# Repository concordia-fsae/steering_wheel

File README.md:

### This code now has Travis CI setup for continuous integration testing!
Current build status: 

# Setup Instructions
  1. Setup PlatformIO in IDE of choice (i.e. VSCode)
  2. Navigate to PlatformIO install directory (usually User_folder/.platformio)
  3. Enter `packages` directory and rename `framework-arduinoststm32-maple` to `framework-arduinoststm32-maple-bak`
  4. Clone [Roger Clark's repo](https://github.com/rogerclarkmelbourne/Arduino_STM32) into the packages directory (`git clone https://github.com/rogerclarkmelbourne/Arduino_STM32.git framework-arduinoststm32-maple`)
  5. Copy `platformio-build-stm32f4.py` and `platformio-build-stm32f1.py` from `framework-arduinoststm32-maple-bak/tools` to `framework-arduinoststm32-maple/tools`
  6. Compile successfully (hopefully)

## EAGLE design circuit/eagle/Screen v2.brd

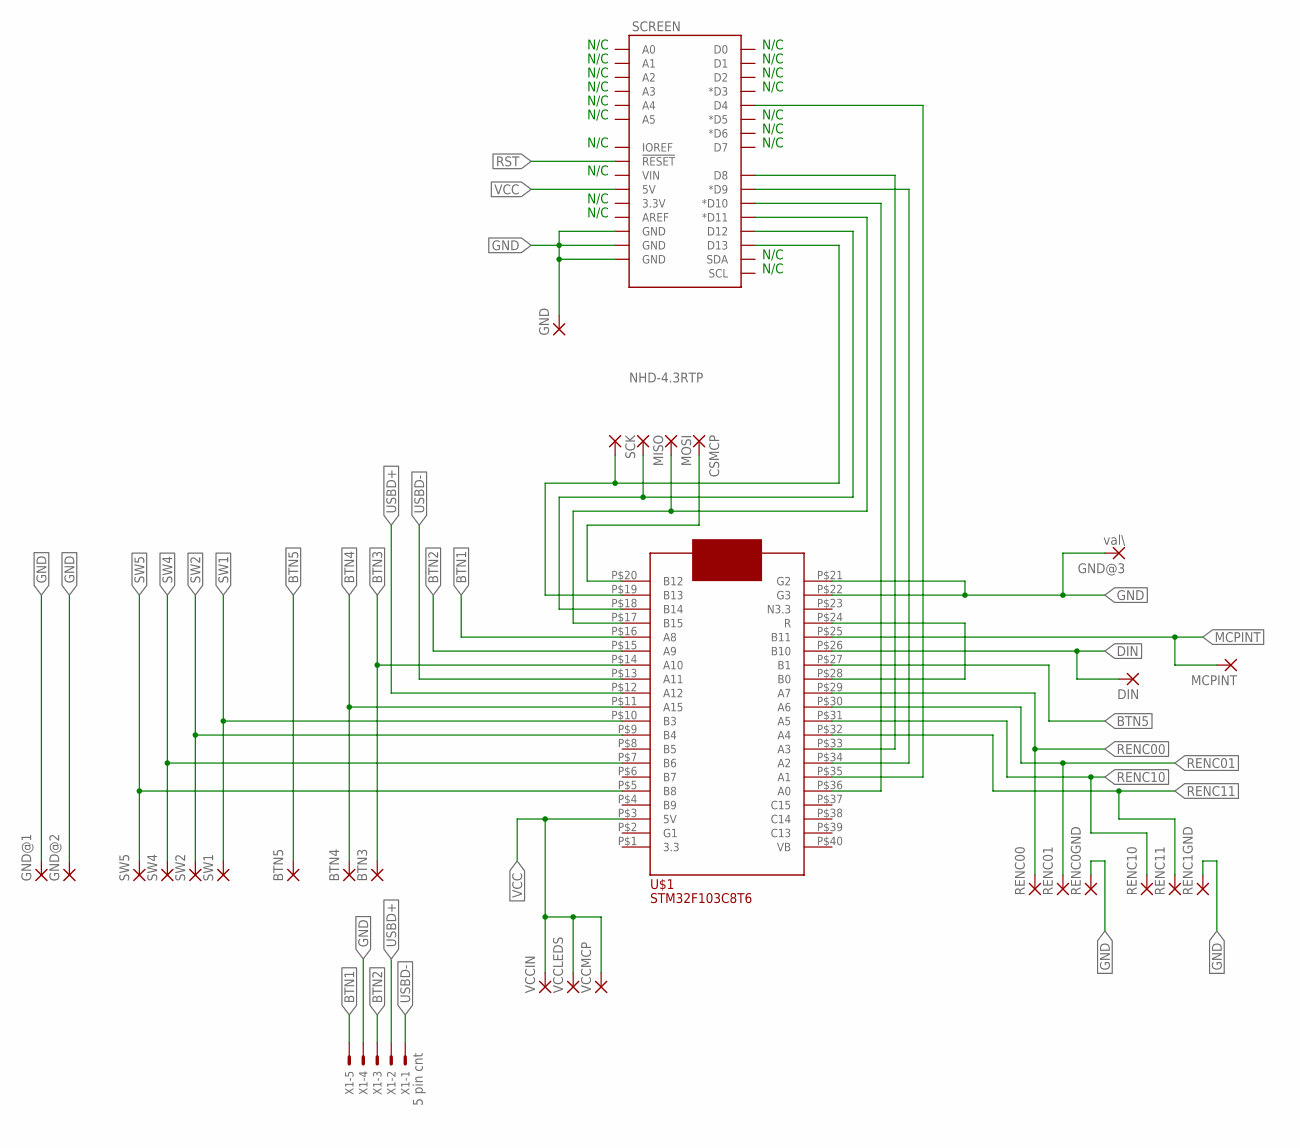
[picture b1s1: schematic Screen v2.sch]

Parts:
BTN3, BTN4, BTN5: SMD5; SMD2,54-5,08
CSMCP: SMD5; SMD2,54-5,08
DIN: SMD5; SMD2,54-5,08
GND: SMD5; SMD2,54-5,08
GND@1, GND@2: SMD5; SMD2,54-5,08
GND@3: val\; SMD2,54-5,08
MCPINT: SMD5; SMD2,54-5,08
MISO: SMD5; SMD2,54-5,08
MOSI: SMD5; SMD2,54-5,08
RENC00, RENC0GND, RENC01, RENC1GND, RENC10, RENC11: SMD5; SMD2,54-5,08
SCK: SMD5; SMD2,54-5,08
SCREEN: NHD-4.3RTP
SW1, SW2, SW4, SW5: SMD5; SMD2,54-5,08
U$1: STM32F103C8T6DIP40; STM32
VCCIN: SMD5; SMD2,54-5,08
VCCLEDS: SMD5; SMD2,54-5,08
VCCMCP: SMD5; SMD2,54-5,08
X1: 5 pin cnt; JST-XH-05-PACKAGE-ROUND-PAD

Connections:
BTN1: U$1.P$16 (A8), X1.5
BTN2: U$1.P$15 (A9), X1.3
BTN3: BTN3.1, U$1.P$14 (A10)
BTN4: BTN4.1, U$1.P$11 (A15)
BTN5: BTN5.1, U$1.P$27 (B1)
CSMCP: CSMCP.1, U$1.P$20 (B12)
CS_SCREEN: SCREEN.D10 (*D10), U$1.P$36 (A0)
DIN: DIN.1, U$1.P$26 (B10)
GND: GND.1, GND@1.1, GND@2.1, GND@3.1, RENC0GND.1, RENC1GND.1, SCREEN.GND@1 (GND), SCREEN.GND@2 (GND), SCREEN.GND@3 (GND), U$1.P$21 (G2), U$1.P$22 (G3), X1.4
MCPINT: MCPINT.1, U$1.P$25 (B11)
MISO: MISO.1, SCREEN.D12, U$1.P$18 (B14)
MOSI: MOSI.1, SCREEN.D11 (*D11), U$1.P$17 (B15)
unnamed: SCREEN.D4, U$1.P$35 (A1)
unnamed: SCREEN.D9 (*D9), U$1.P$34 (A2)
unnamed: SCREEN.D8, U$1.P$33 (A3)
unnamed: U$1.P$24 (R), U$1.P$28 (B0)
RENC00: RENC00.1, U$1.P$29 (A7)
RENC01: RENC01.1, U$1.P$30 (A6)
RENC10: RENC10.1, U$1.P$31 (A5)
RENC11: RENC11.1, U$1.P$32 (A4)
RST: SCREEN.RESET@1 (!RESET!)
SCK: SCK.1, SCREEN.D13, U$1.P$19 (B13)
SW1: SW1.1, U$1.P$10 (B3)
SW2: SW2.1, U$1.P$9 (B4)
SW4: SW4.1, U$1.P$7 (B6)
SW5: SW5.1, U$1.P$5 (B8)
USBD+: U$1.P$12 (A12), X1.2
USBD-: U$1.P$13 (A11), X1.1
VCC: SCREEN.5V, U$1.P$3 (5V), VCCIN.1, VCCLEDS.1, VCCMCP.1

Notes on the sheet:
N/C

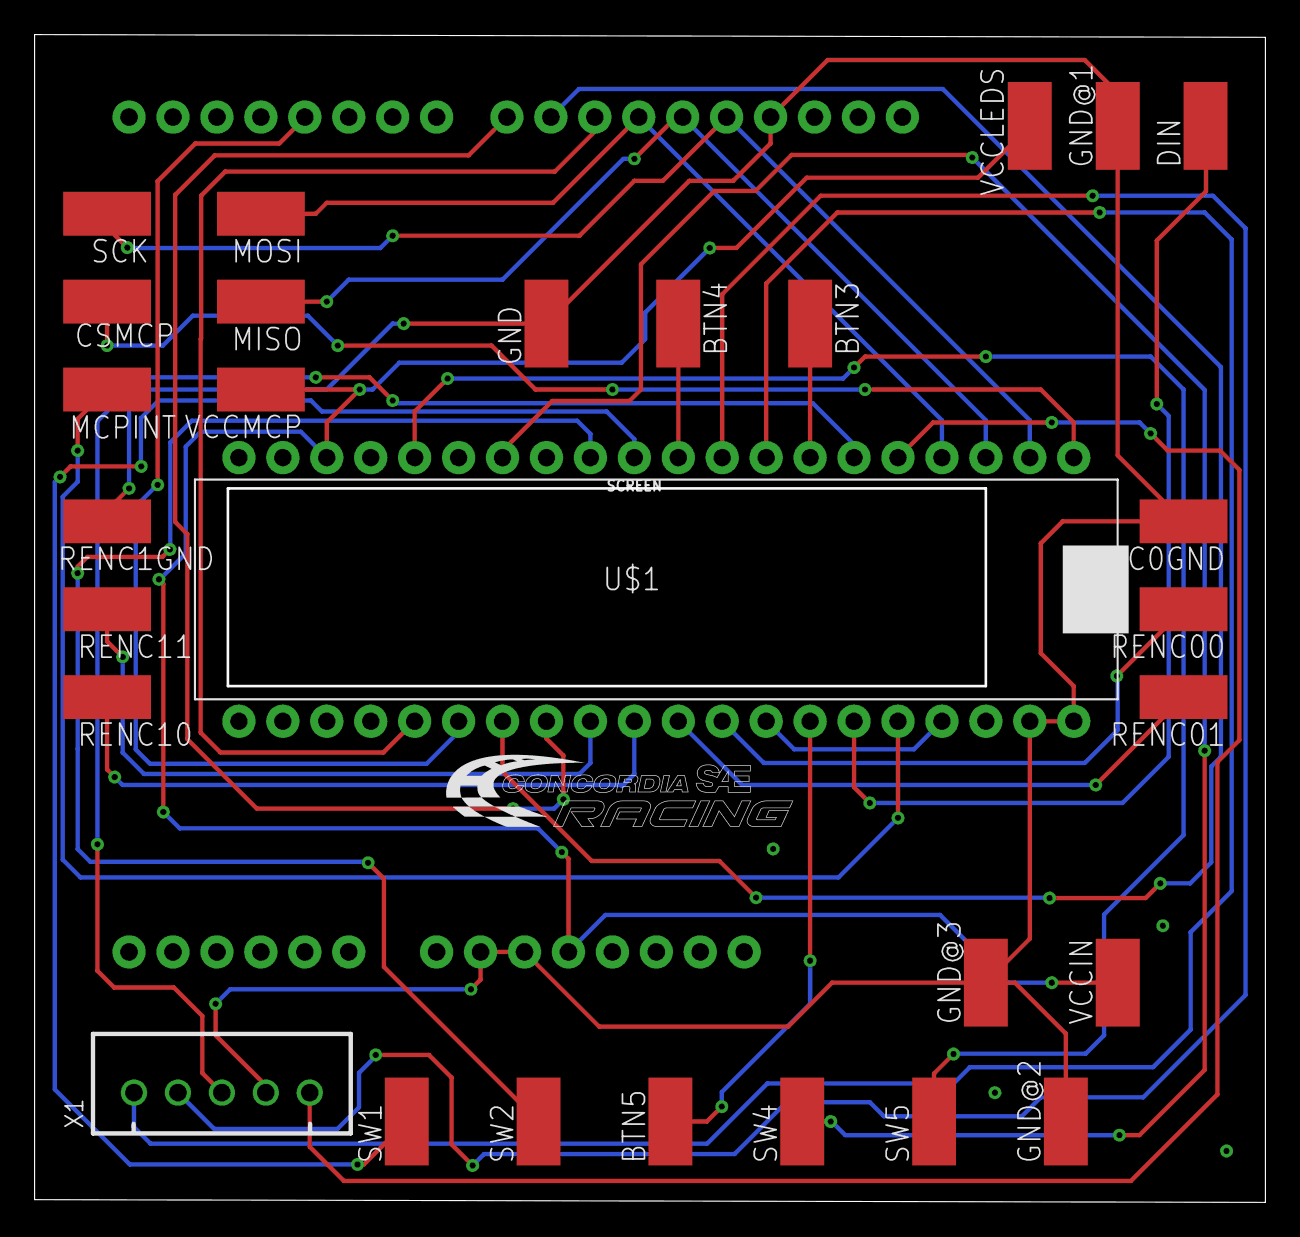
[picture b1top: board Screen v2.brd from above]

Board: 2 copper layers, 71.0 x 67.4 mm, 29 parts (0 on the bottom side), 28 nets.

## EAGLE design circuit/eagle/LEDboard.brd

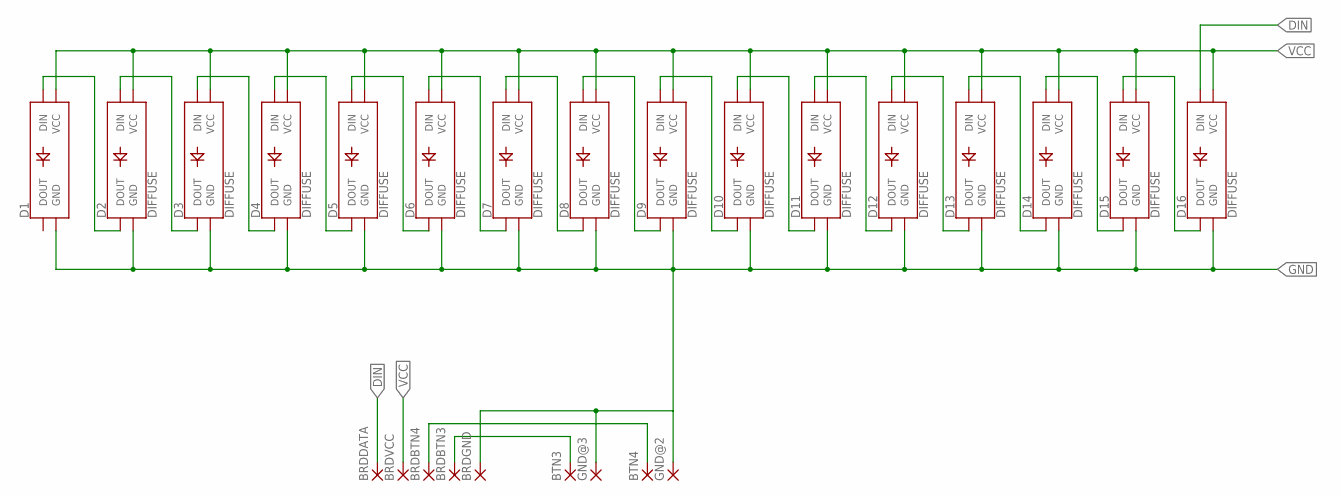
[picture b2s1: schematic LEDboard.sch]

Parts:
BRDBTN3, BRDBTN4: SMD5; SMD2,54-5,08
BRDDATA: SMD5; SMD2,54-5,08
BRDGND: SMD5; SMD2,54-5,08
BRDVCC: SMD5; SMD2,54-5,08
BTN3, BTN4: SMD5; SMD2,54-5,08
D1: WS2812B_THT_ROUNDDIFFUSE; WS2812B_THT_ROUND
D2, D3, D4, D5, D6, D7, D8, D9, D10, D11, D12, D13, D14, D15, D16: DIFFUSE; WS2812B_THT_ROUND
GND@2, GND@3: SMD5; SMD2,54-5,08

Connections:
BTN3: BRDBTN3.1, BTN3.1
BTN4: BRDBTN4.1, BTN4.1
DIN: BRDDATA.1, D16.1 (DIN)
GND: BRDGND.1, D1.3 (GND), D2.3 (GND), D3.3 (GND), D4.3 (GND), D5.3 (GND), D6.3 (GND), D7.3 (GND), D8.3 (GND), D9.3 (GND), D10.3 (GND), D11.3 (GND), D12.3 (GND), D13.3 (GND), D14.3 (GND), D15.3 (GND), D16.3 (GND), GND@2.1, GND@3.1
unnamed: D15.1 (DIN), D16.4 (DOUT)
unnamed: D14.1 (DIN), D15.4 (DOUT)
unnamed: D13.1 (DIN), D14.4 (DOUT)
unnamed: D12.1 (DIN), D13.4 (DOUT)
unnamed: D11.1 (DIN), D12.4 (DOUT)
unnamed: D10.1 (DIN), D11.4 (DOUT)
unnamed: D9.1 (DIN), D10.4 (DOUT)
unnamed: D8.1 (DIN), D9.4 (DOUT)
unnamed: D7.1 (DIN), D8.4 (DOUT)
unnamed: D6.1 (DIN), D7.4 (DOUT)
unnamed: D5.1 (DIN), D6.4 (DOUT)
unnamed: D4.1 (DIN), D5.4 (DOUT)
unnamed: D3.1 (DIN), D4.4 (DOUT)
unnamed: D2.1 (DIN), D3.4 (DOUT)
unnamed: D1.1 (DIN), D2.4 (DOUT)
VCC: BRDVCC.1, D1.2 (VCC), D2.2 (VCC), D3.2 (VCC), D4.2 (VCC), D5.2 (VCC), D6.2 (VCC), D7.2 (VCC), D8.2 (VCC), D9.2 (VCC), D10.2 (VCC), D11.2 (VCC), D12.2 (VCC), D13.2 (VCC), D14.2 (VCC), D15.2 (VCC), D16.2 (VCC)

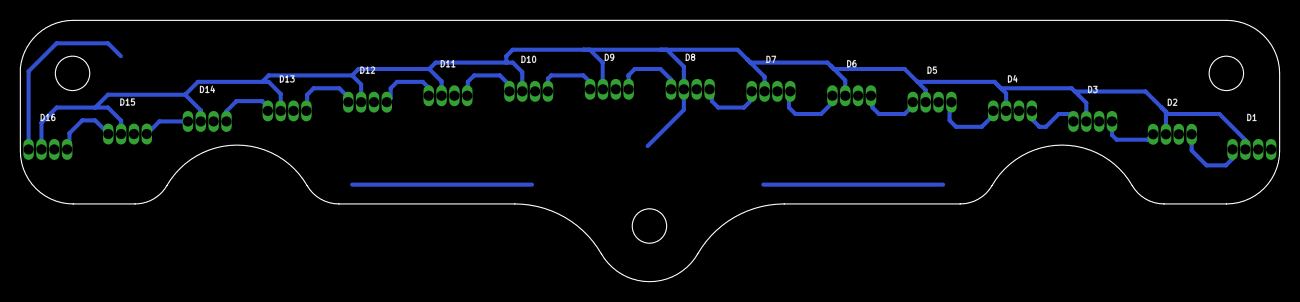
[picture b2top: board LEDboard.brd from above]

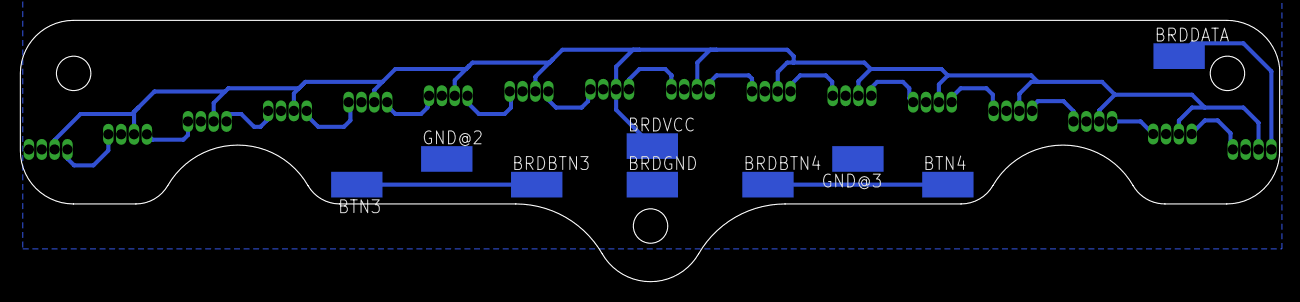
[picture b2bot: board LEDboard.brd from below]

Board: 2 copper layers, 124.5 x 25.8 mm, 25 parts (9 on the bottom side), 20 nets.

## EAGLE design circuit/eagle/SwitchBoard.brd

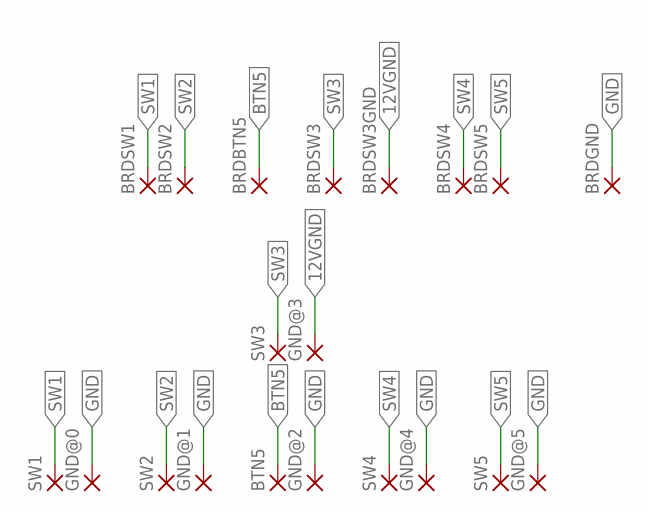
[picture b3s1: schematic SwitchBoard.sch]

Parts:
BRDBTN5: SMD5; SMD2,54-5,08
BRDGND: SMD5; SMD2,54-5,08
BRDSW1, BRDSW2, BRDSW3, BRDSW3GND, BRDSW4, BRDSW5: SMD5; SMD2,54-5,08
BTN5: SMD5; SMD2,54-5,08
GND@0, GND@1, GND@2, GND@3, GND@4, GND@5: SMD5; SMD2,54-5,08
SW1, SW2, SW3, SW4, SW5: SMD5; SMD2,54-5,08

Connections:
12VGND: BRDSW3GND.1, GND@3.1
BTN5: BRDBTN5.1, BTN5.1
GND: BRDGND.1, GND@0.1, GND@1.1, GND@2.1, GND@4.1, GND@5.1
SW1: BRDSW1.1, SW1.1
SW2: BRDSW2.1, SW2.1
SW3: BRDSW3.1, SW3.1
SW4: BRDSW4.1, SW4.1
SW5: BRDSW5.1, SW5.1

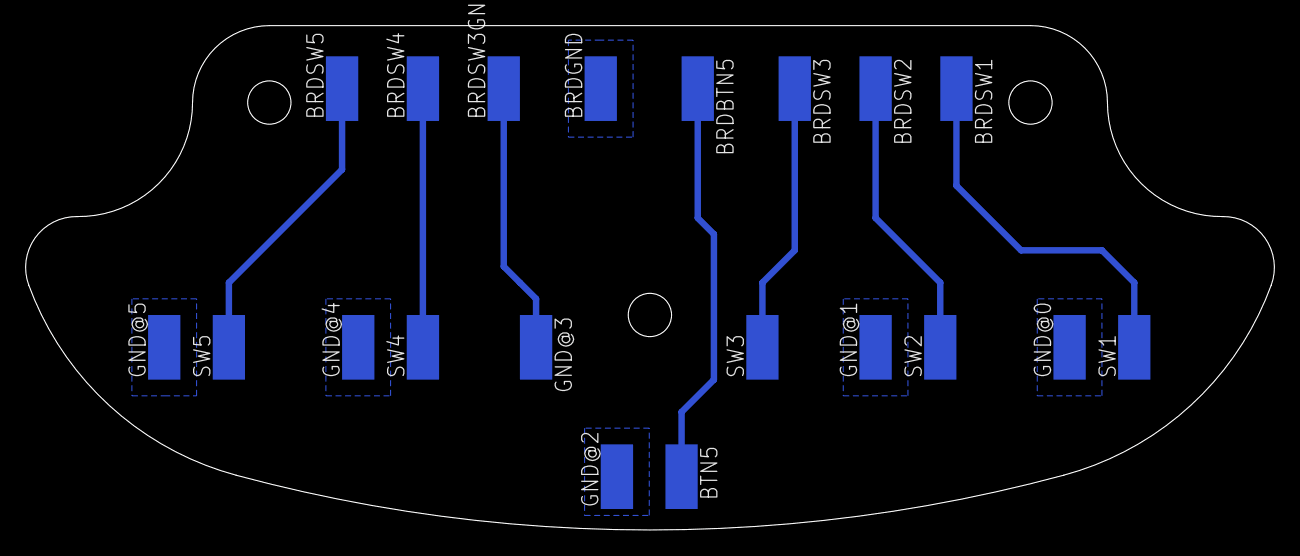
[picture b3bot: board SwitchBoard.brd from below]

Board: 2 copper layers, 98.1 x 39.6 mm, 20 parts (20 on the bottom side), 8 nets.

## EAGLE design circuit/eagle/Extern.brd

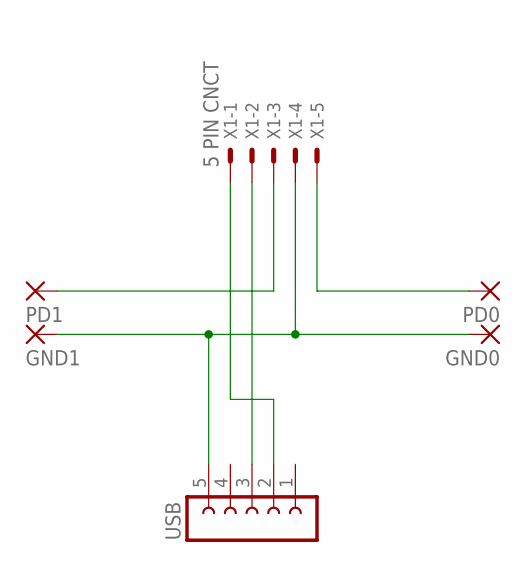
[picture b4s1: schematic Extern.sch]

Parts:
GND0, GND1: SMD5; SMD2,54-5,08
PD0, PD1: SMD5; SMD2,54-5,08
USB: FE05-1
X1: 5 PIN CNCT; JST-XH-05-PACKAGE-ROUND-PAD

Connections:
D+: USB.3, X1.2
D-: USB.2, X1.1
GND: GND0.1, GND1.1, USB.5, X1.4
unnamed: PD0.1, X1.5
PD1: PD1.1, X1.3

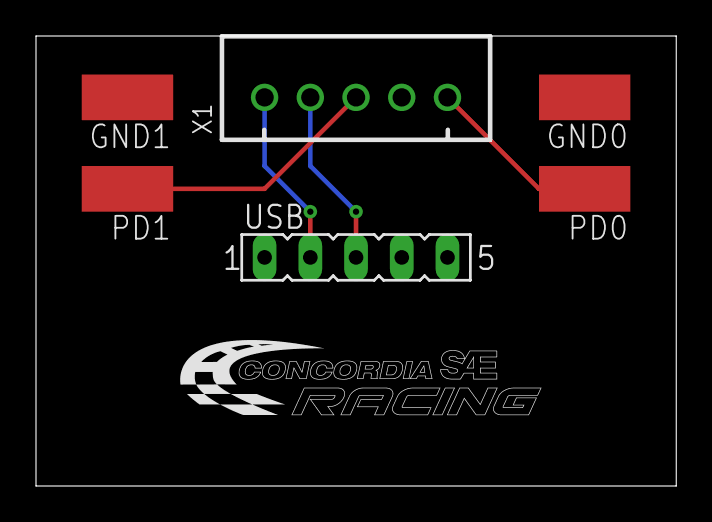
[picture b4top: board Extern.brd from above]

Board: 2 copper layers, 35.6 x 25.0 mm, 6 parts (0 on the bottom side), 5 nets.

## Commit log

2019-04-08 initial commit with all existing code and layouts
2019-05-22 switched to platformio
2019-05-22 platformio migration
2020-07-07 minor cleanup
2020-07-21 update gitignore
2020-07-21 Restructure code
    Separate code into separate files in order to simplify everything. Still has work to be done, but better now.
    Also rewrote shiftlight code to make it not awful.
2020-08-18 fix vscode compile errors
2020-08-29 delete .directory
    linux artifact, not necessary
2020-08-29 added comments and restructured code into separate units. Still need to separate functions out of h files into c files
2020-08-30 made a bunch of optimizations
2020-08-30 more optimization
2020-09-01 Example to show how to commit and push
2020-09-01 I made an empty class called 5Head to learn how to be less 5Head
2020-09-01 Another commit to demonstrate
2020-09-01 More examples
2020-09-01 Beginning of timer.h and timer.cpp files. Starting update() method and trying to make frequency flexible and not hard-coded
2020-09-01 #11 general optimization. changed abiguous variable type definitions in main.h so that they are specific
2020-09-01 trying to set up travisCI
2020-09-01 added travis CI build info to readme
2020-09-02 Defined structs for all of the data and refactored so that it compiles. Definitely a lot of cleanup that is possible now that NEEDS to happen, but it's bedtime
2020-09-03 restructured all of the globals containing car info into structs, everything is now contained within the global. Also separated canbus.h into canbus.h + canbus.cpp. This issue should be closed for no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
2020-09-04 addresses #26, decided a function isn't necessary since v_fl and f_int are only used in one place and a function call would be pointless. considered a static inline, but again, no point as it would o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
2020-09-04 Moved the struct I made yesterday for vehicle data into a separate header file so I can include it all over the place without having to worry about redefining stuff
2020-09-04 got it to compile, the only real problem was the SPI was being defined somewhere in the FT800 headers when it shouldn't have been. Sorted by making that definition extern and moving the real definiti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
2020-09-05 addresses #16, simple bug which has been fixed. I think pin B3 might be blown on my test setup because it's not tripping the wheel circumference flag but I can't find any code mistakes. Either way, i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
2020-09-05 added and tested Debouncer class, seems to work I think it's pretty clever tbh pertains to #7
2020-09-05 implemented the debouncer class I added. Also modified it a bit for some extra functionality Fully replaced all references to other types of debouncing with references to this class, tested everythin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
2020-09-15 Add existing circuit files
2020-09-15 Made initial FT810 schematic Still needs passives to be specified from suppliers Should include everything on the FT side of things, just needs micro Still unsure about the two extra pins for QSPI...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
2020-09-29 Initial design is almost done. Still have to add USB support.
    Still related to #34
2020-09-30 sch done, have to replace all dummy components
2020-10-03 Sch is done (or close to it) making good progress on board as well.
2020-10-04 Almost done with board too
2020-10-05 Board is done except for positioning the contacts Center contacts need to be positioned such that they match where the pogo pins will end up making contact
2020-10-06 touchscreen calibration now done with EEPROM! Automatically loads cal values from eeprom instead of using defaults if the eeprom is empty or faulted, loads the defaults this means that we can now add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
    Also made MasterConfig.h and started moving some #defines there. This
    file will basically contain all the settings that you might want to
    change
    Added preprocessor-controlled debug blocks. If you want to debug, set
    the appropriate values in MasterConfig.h and the debug code will be
    compiled. If you don't want to debug, the code won't even be compiled!
2020-10-06 redefined c_time c_time now reports the value of systick_uptime_millis, which means we should _never_ need to update c_time any more! It should always contain the most up to date value. This will pro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
2020-10-10 Bug #37 - Fix SPI frequency too high for FT800
2020-10-17 Bug #37 - Fix SPI frequency too high for FT800 (#38)
2020-12-31 removing circuits and closing branch. See #34 for details
2020-12-31 Removing circuit from this repo. Will add to different repo. (#43)
    * Made initial FT810 schematic
    Still needs passives to be specified from suppliers
    Should include everything on the FT side of things, just needs micro
    Still unsure about the two extra pins for QSPI...
    pertains to #34
    * Initial design is almost done.
